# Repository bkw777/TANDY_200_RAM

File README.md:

# Option RAM module for TANDY 200

Replacements for TANDY 26-3866 24K SRAM module for TANDY 200 portable computer.

There are a few different options here. You pick whichever you need.  
* Single-bank, SOP-28 chip - Drop-in replacement for the original 24K module, with a large-ish chip that's relatively easy to solder by hand. Use this if you already have one original ceramic module, and want to keep using it, and just want one more 24K module to fill the machine, and you prefer to use, or happen to already have an SOIC-28/SOP-28 version of the SRAM chip.
* Single-bank, TSOP-28 chip - Same as above but uses a TSOP version of the SRAM chip.
* Dual-bank, SOP-32 chip - This provides the full 48 as 2 normal 24K modules all on one board. You plug a single one of these into OPTION RAM#2 slot. Uses an SOIC-32/SOP-32 chip for easier hand soldering.
* Dual-bank, TSOP-32 chip - Same as above but uses a TSOP version of the SRAM chip. These are more common and more available, but also more of a challenge to solder by hand.

The holes for the pins are intentionally too small to accept common square or round pins, as they are too fat and damage the leaf-style sockets in the 200. The BOMs include a specific pin that is extra thin, almost as thin as a dip chip leg. You may also use a SIL leadframe that has flat pins exactly like a DIP chip leg. See this [dip pcb legs guide](https://gist.github.com/bkw777/52d85d89eeff8445cc667685d05ea94d) for more details and links.

<!--
There are a few different designs available that all do the same thing but using different parts.

Some variants are single-bank like the original TANDY 26-3866 ceramic 24k module. These are drop-in replacements for the original modules, where one board = one bank = one Option RAM socket. You can have up to two boards installed in the machine.

Some variants are dual-bank, where one board supplies both Option RAM bank #1 and #2. You plug the one board into the Option RAM #2 socket, and this takes the place of two single-bank modules.

Some variants use different chip packages, so that you have options to use whatever types of chip you have, or can get, or can solder by hand.

There is also a [schematic of the original RAM bank](TANDY_26-3866.svg), re-drawn in KiCAD just for reference. There is no PCB for this, it's just for reference while designing new replacement modules to help ensure the replacement really still outwardly works the same as the original.
-->

See the [releases](../../releases) tab for gerber zips for manufacturing.  
If there is no link to order a pcb for one of the versions below, it means that design isn't tested and proven yet.

## Single-Bank - SOP

<!-- PCB from [OSHPark](),  or  [PCBWAY](),  or  [gerbers](../../releases/latest/)  -->
BOM from [DigiKey](https://www.digikey.com/short/f5hhwt4j),  or  [TANDY_200_RAM.BOM.csv](TANDY_200_RAM.BOM.csv)  

## Single-Bank - TSOP

<!--    -->

<!--
PCB from [OSHPark](),  or  [PCBWAY](),  or  [gerbers](../../releases/latest)  
BOM from [DigiKey](),  or  [BOM.csv]()  
-->

<!--
## Single-Bank THT DIP

PCB from [OSHPark](),  or  [PCBWAY](),  or  [gerbers](../../releases/latest)  
BOM from [DigiKey](),  or  [BOM.csv]()  
-->

## Dual-Bank - SOP

<!-- PCB from [OSHPark](),  or  [PCBWAY](),  or  [gerbers](../../releases/latest/)  -->  
BOM from [DigiKey](https://www.digikey.com/short/25v45c90),  or  [TANDY_200_Dual_RAM.BOM.csv](TANDY_200_Dual_RAM.BOM.csv)  

## Dual-Bank - TSOP

Supports both TSOP-32 (20mm) and sTSOP-32 (14mm).  

PCB from <!-- [OSHPark](),  or  -->[PCBWAY](https://www.pcbway.com/project/shareproject/TANDY_200_RAM_48K_TSOP_57aa6fd6.html),  or  [gerbers](../../releases/latest)  
BOM from [DigiKey](https://www.digikey.com/short/bvrwht5d),  or  [TANDY_200_Dual_RAM_tsop.BOM.csv](TANDY_200_Dual_RAM_tsop.BOM.csv)  

<!--
## Dual-Bank THT DIP

PCB from [OSHPark](),  or  [PCBWAY](),  or  [gerbers](../../releases/latest)  
BOM from [DigiKey](),  or  [BOM.csv]()  
-->

## Original TANDY 26-3866 24K Option RAM for reference  
Re-drawn in KiCAD from the info in the service manual.  
This is what any alternative must replicate or emulate.  
The internal 24K bank is also the same (without the ceramic DIP carrier module).

## Misc Notes  
Memory Tester app for TANDY 200  
https://github.com/LivingM100SIG/Living_M100SIG/blob/main/M100SIG/Lib-10-TANDY200/MEMCHK.200  
https://github.com/LivingM100SIG/Living_M100SIG/blob/main/M100SIG/Lib-10-TANDY200/MEMCHK.SRC

The BOM includes Mill-Max 3121 machined brass micro pins, but there are a couple of other ways to make properly thin [PCB DIP legs](https://gist.github.com/bkw777/52d85d89eeff8445cc667685d05ea94d) .

The DIP row spacing is actually 725 mils not 700. This makes it a little bit annoying to solder the legs because the rows don't line up exactly with the 100-mil rows in a breadboard, but the odd spacing is deliberate not an arror.  

Suggestion for soldering the pins:  
Use some generic single-row female pin headers in a breadboard to hold the pins in alignment for soldering.  
Take 2 rows of 28 pins of single-row female pin headers and insert them into a breadboard 600 mils apart like for a normal 600 mil dip.  
One row is for holding pins, the other will not line up with the other row of holes, it is just for the pcb to rest on to hold up the other side of the pcb so it's level.  
Dip the post end of a pin in tacky solder paste, and insert into a hole in the pcb. Let the flux hold the pin in the pcb, don't worry about how loose the fit is and how the pin isn't held perfectly straight. Repeat for all 14 pins of ONE row of the pcb.
Insert the row of pins into one of the female sockets on the breadboard, laying the pcb across the top of the other socket. Solder the pins from the top.  
Extract the pcb from the socket and repeat for the other row of 14 pins. Finally do the single pin.  
The pins are very fragile. Be careful not to let them get bent, because they don't bend much before they break, and they bend easily, so just be real careful not to let anything catch on them and be careful when extracting from sockets not to allow the pcb to tip and angle.

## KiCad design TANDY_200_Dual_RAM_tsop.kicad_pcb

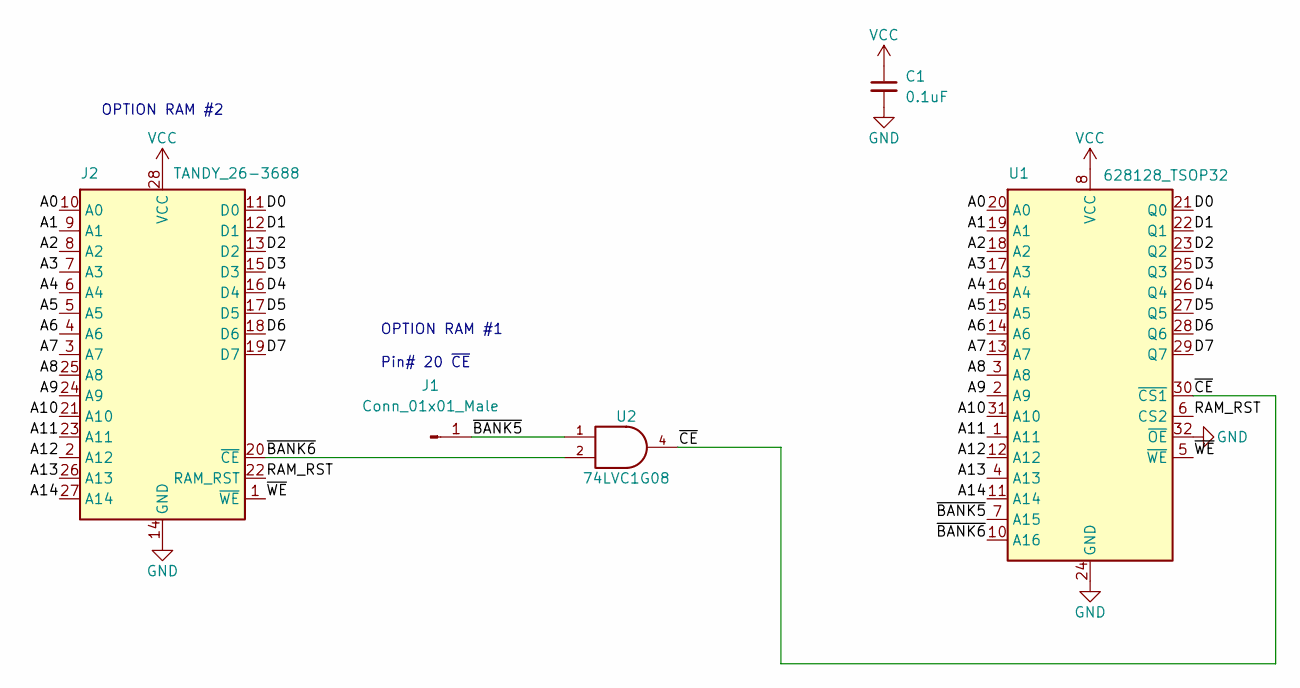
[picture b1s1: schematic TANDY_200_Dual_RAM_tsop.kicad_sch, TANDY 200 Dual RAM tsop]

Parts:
C1: 0.1uF; C_0805
J1: Conn_01x01_Male; Mill-Max 3121
J2: TANDY_26-3688; KEL ICC05-028-360TP
U1: 628128_TSOP32; TSOP32-dual
U2: 74LVC1G08; SOT-23-5

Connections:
/A0: J2.10 (A0), U1.20 (A0)
/A1: J2.9 (A1), U1.19 (A1)
/A2: J2.8 (A2), U1.18 (A2)
/A3: J2.7 (A3), U1.17 (A3)
/A4: J2.6 (A4), U1.16 (A4)
/A5: J2.5 (A5), U1.15 (A5)
/A6: J2.4 (A6), U1.14 (A6)
/A7: J2.3 (A7), U1.13 (A7)
/A8: J2.25 (A8), U1.3 (A8)
/A9: J2.24 (A9), U1.2 (A9)
/A10: J2.21 (A10), U1.31 (A10)
/A11: J2.23 (A11), U1.1 (A11)
/A12: J2.2 (A12), U1.12 (A12)
/A13: J2.26 (A13), U1.4 (A13)
/A14: J2.27 (A14), U1.11 (A14)
/D0: J2.11 (D0), U1.21 (Q0)
/D1: J2.12 (D1), U1.22 (Q1)
/D2: J2.13 (D2), U1.23 (Q2)
/D3: J2.15 (D3), U1.25 (Q3)
/D4: J2.16 (D4), U1.26 (Q4)
/D5: J2.17 (D5), U1.27 (Q5)
/D6: J2.18 (D6), U1.28 (Q6)
/D7: J2.19 (D7), U1.29 (Q7)
/RAM_RST: J2.22 (RAM_RST), U1.6 (CS2)
/~BANK5: J1.1, U1.7 (A15), U2.1
/~BANK6: J2.20 (~CE), U1.10 (A16), U2.2
/~CE: U1.30 (~CS1), U2.4
/~WE: J2.1 (~WE), U1.5 (~WE)
GND: C1.2, J2.14 (GND), U1.24 (GND), U1.32 (~OE), U2.3 (GND)
VCC: C1.1, J2.28 (VCC), U1.8 (VCC), U2.5 (VCC)

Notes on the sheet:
OPTION RAM #1 Pin# 20 ~{CE}
OPTION RAM #2

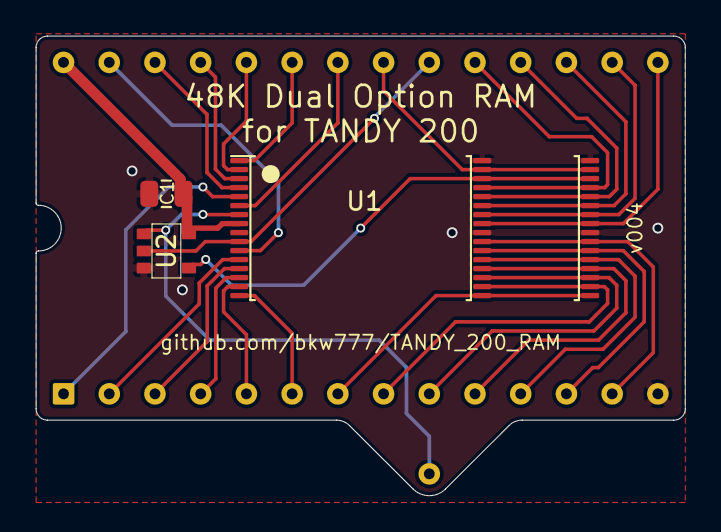
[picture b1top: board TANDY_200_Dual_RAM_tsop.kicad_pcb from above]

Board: 2 copper layers, 36.1 x 25.5 mm, 5 parts (0 on the bottom side), 30 nets.

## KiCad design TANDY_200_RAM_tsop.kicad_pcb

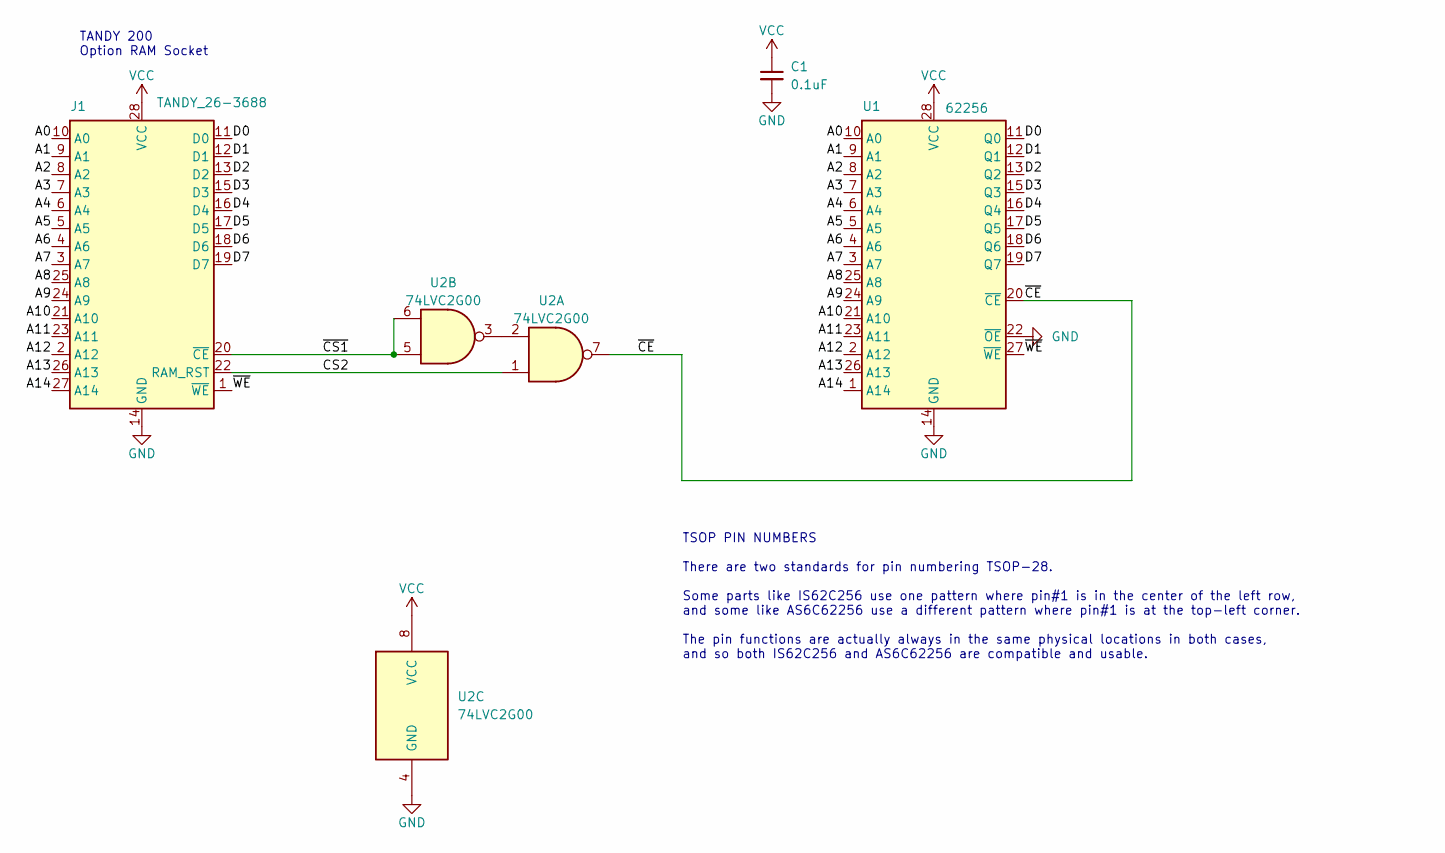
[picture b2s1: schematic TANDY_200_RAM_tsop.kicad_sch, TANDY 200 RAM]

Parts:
C1: 0.1uF; C_0805
J1: TANDY_26-3688; KEL ICC05-028-360TP
U1: 62256; TSOP-28
U2: 74LVC2G00; SSOP-8_2.95x2.8x0.65

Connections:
/A0: J1.10 (A0), U1.10 (A0)
/A1: J1.9 (A1), U1.9 (A1)
/A2: J1.8 (A2), U1.8 (A2)
/A3: J1.7 (A3), U1.7 (A3)
/A4: J1.6 (A4), U1.6 (A4)
/A5: J1.5 (A5), U1.5 (A5)
/A6: J1.4 (A6), U1.4 (A6)
/A7: J1.3 (A7), U1.3 (A7)
/A8: J1.25 (A8), U1.25 (A8)
/A9: J1.24 (A9), U1.24 (A9)
/A10: J1.21 (A10), U1.21 (A10)
/A11: J1.23 (A11), U1.23 (A11)
/A12: J1.2 (A12), U1.2 (A12)
/A13: J1.26 (A13), U1.26 (A13)
/A14: J1.27 (A14), U1.1 (A14)
/CS2: J1.22 (RAM_RST), U2.1
/D0: J1.11 (D0), U1.11 (Q0)
/D1: J1.12 (D1), U1.12 (Q1)
/D2: J1.13 (D2), U1.13 (Q2)
/D3: J1.15 (D3), U1.15 (Q3)
/D4: J1.16 (D4), U1.16 (Q4)
/D5: J1.17 (D5), U1.17 (Q5)
/D6: J1.18 (D6), U1.18 (Q6)
/D7: J1.19 (D7), U1.19 (Q7)
/~CE: U1.20 (~CE), U2.7
/~CS1: J1.20 (~CE), U2.5, U2.6
/~WE: J1.1 (~WE), U1.27 (~WE)
GND: C1.2, J1.14 (GND), U1.14 (GND), U1.22 (~OE), U2.4 (GND)
unnamed: U2.2, U2.3
VCC: C1.1, J1.28 (VCC), U1.28 (VCC), U2.8 (VCC)

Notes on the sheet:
TANDY 200 Option RAM Socket
TSOP PIN NUMBERS There are two standards for pin numbering TSOP-28. Some parts like IS62C256 use one pattern where pin#1 is in the center of the left row, and some like AS6C62256 use a different pattern where pin#1 is at the top-left corner. The pin functions are actually always in the same physica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

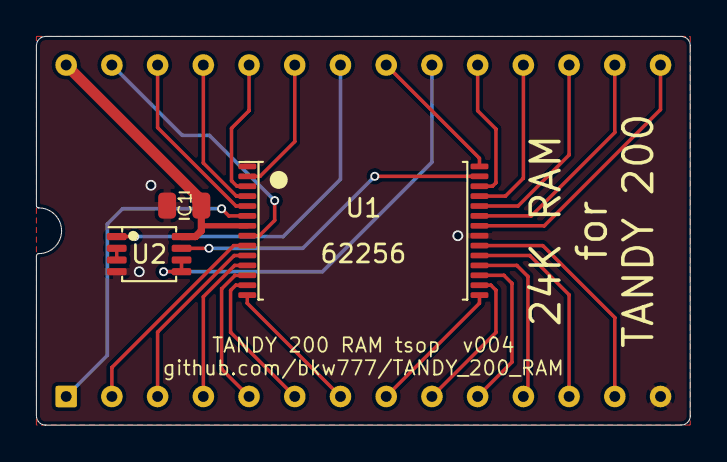
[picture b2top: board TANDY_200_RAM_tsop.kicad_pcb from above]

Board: 2 copper layers, 36.3 x 21.6 mm, 4 parts (0 on the bottom side), 30 nets.

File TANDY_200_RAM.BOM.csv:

"Index","Quantity","Part Number","Manufacturer Part Number","Description","Customer Reference","Available","Backorder","Unit Price","Extended Price USD"
"1","1","1450-1034-ND","AS6C62256-55SCN","IC SRAM 256KBIT PARALLEL 28SOP","","1","0","3.45000","3.45"
"2","1","1727-5985-1-ND","74LVC2G00DP,125","IC GATE NAND 2CH 2-INP 8TSSOP","","1","0","0.61000","0.61"
"3","1","732-8045-1-ND","885012207045","CAP CER 0.1UF 16V X7R 0805","","1","0","0.10000","0.10"
"4","28","ED1081-ND","3121-2-00-15-00-00-08-0","CONN PC PIN CIRC 0.017DIA GOLD","","28","0","0.11480","3.21"

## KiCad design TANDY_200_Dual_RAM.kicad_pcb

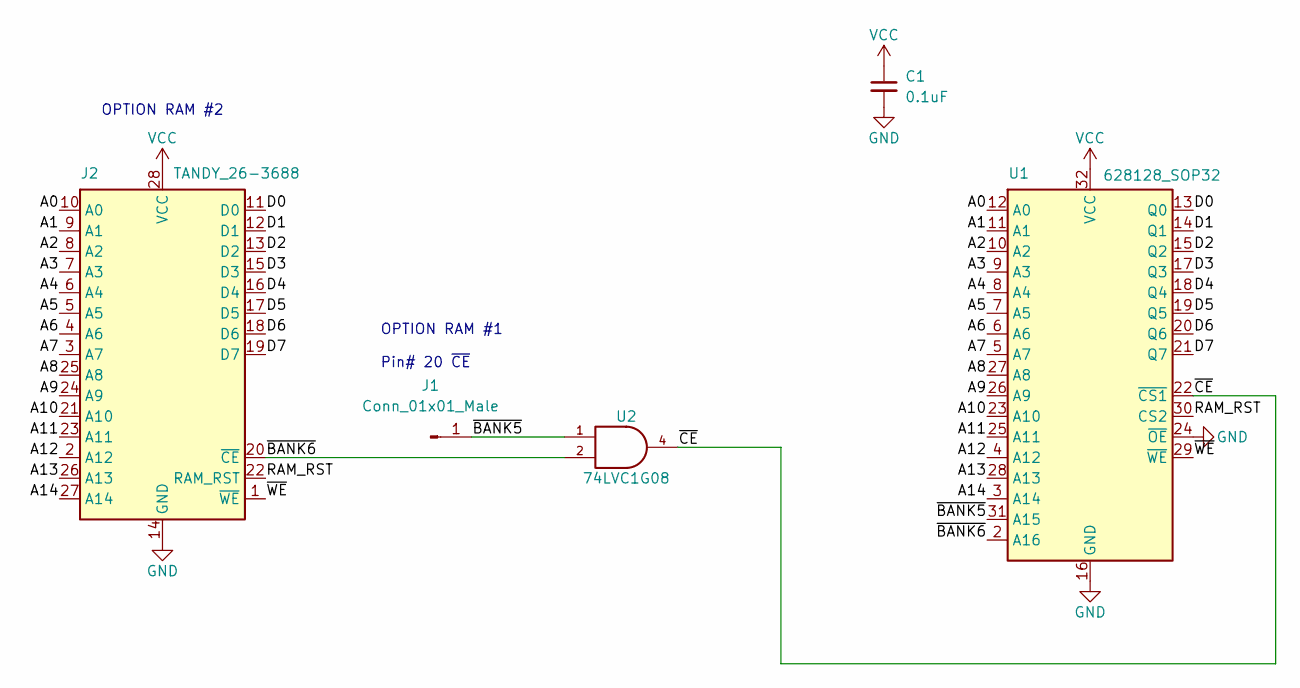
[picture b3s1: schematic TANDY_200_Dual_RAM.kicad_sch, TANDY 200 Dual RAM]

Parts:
C1: 0.1uF; C_0805
J1: Conn_01x01_Male; Mill-Max 3121
J2: TANDY_26-3688; KEL ICC05-028-360TP
U1: 628128_SOP32; SOP-32
U2: 74LVC1G08; SOT-23-5

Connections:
/A0: J2.10 (A0), U1.12 (A0)
/A1: J2.9 (A1), U1.11 (A1)
/A2: J2.8 (A2), U1.10 (A2)
/A3: J2.7 (A3), U1.9 (A3)
/A4: J2.6 (A4), U1.8 (A4)
/A5: J2.5 (A5), U1.7 (A5)
/A6: J2.4 (A6), U1.6 (A6)
/A7: J2.3 (A7), U1.5 (A7)
/A8: J2.25 (A8), U1.27 (A8)
/A9: J2.24 (A9), U1.26 (A9)
/A10: J2.21 (A10), U1.23 (A10)
/A11: J2.23 (A11), U1.25 (A11)
/A12: J2.2 (A12), U1.4 (A12)
/A13: J2.26 (A13), U1.28 (A13)
/A14: J2.27 (A14), U1.3 (A14)
/D0: J2.11 (D0), U1.13 (Q0)
/D1: J2.12 (D1), U1.14 (Q1)
/D2: J2.13 (D2), U1.15 (Q2)
/D3: J2.15 (D3), U1.17 (Q3)
/D4: J2.16 (D4), U1.18 (Q4)
/D5: J2.17 (D5), U1.19 (Q5)
/D6: J2.18 (D6), U1.20 (Q6)
/D7: J2.19 (D7), U1.21 (Q7)
/RAM_RST: J2.22 (RAM_RST), U1.30 (CS2)
/~BANK5: J1.1, U1.31 (A15), U2.1
/~BANK6: J2.20 (~CE), U1.2 (A16), U2.2
/~CE: U1.22 (~CS1), U2.4
/~WE: J2.1 (~WE), U1.29 (~WE)
GND: C1.2, J2.14 (GND), U1.16 (GND), U1.24 (~OE), U2.3 (GND)
VCC: C1.1, J2.28 (VCC), U1.32 (VCC), U2.5 (VCC)

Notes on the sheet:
OPTION RAM #1 Pin# 20 ~{CE}
OPTION RAM #2

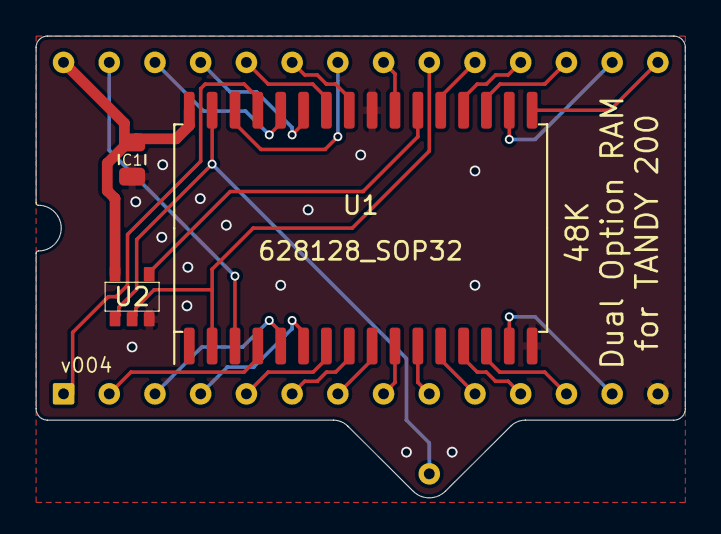
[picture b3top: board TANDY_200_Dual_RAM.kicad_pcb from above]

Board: 2 copper layers, 36.1 x 25.7 mm, 5 parts (0 on the bottom side), 30 nets.

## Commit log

2022-09-16 initial
2022-09-16 readme original 26-3866 module
2022-09-16 ignore .kicad_prl
2022-09-16 add reference docs and project local library
2022-09-16 add boards: single-bank, dual-bank, dual-bank tsop
2022-09-16 readme
2022-09-16 symmetrical part placement
2022-09-17 board outlines, ground planes
2022-09-17 schematic plot backgrounds
2022-09-17 reference pics
2022-09-17 render pics
2022-09-19 add single-bank tsop
2022-09-19 original ram datasheet
2022-09-22 ground paths, footprints, sch symbols
2022-10-02 24k tsop layout and all board outlines expanded slightly
2022-10-02 48k tsop ground pour
2022-10-04 readme, 48k tsop pcb link, pins soldering guide
